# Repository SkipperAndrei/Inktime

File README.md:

# InkTime Watch

Made by: Giurgiu Andrei-Ștefan 335CA

## Cuprins

1. [Prezentare generală](#1-prezentare-generală)
2. [Diagramă bloc](#2-diagramă-bloc)
3. [BOM – Bill of Materials](#3-bom--bill-of-materials)
4. [Descrierea hardware în detaliu](#4-descrierea-hardware-în-detaliu)
5. [Pinout nRF52840 – atribuire completă](#5-pinout-nrf52840--atribuire-completă)
6. [Estimare consum de energie](#6-estimare-consum-de-energie)
7. [Arhitectura firmware](#7-arhitectura-firmware)
8. [Aplicația mobilă companion](#8-aplicația-mobilă-companion)
9. [Randări produs](#9-randări-produs)

---

## 1. Prezentare generală

**InkTime** este un smartwatch conceput pentru a oferi:

- Afișaj e-paper 1.54" (200×200 px) cu refresh parțial o dată pe minut pentru un cadran digital clar, lizibil la orice lumină.
- Notificări BLE de pe telefon (profil tipic: ≤ 50 notificări/zi) cu alerte haptic.
- Numărare pași permanentă prin accelerometru cu pedometru integrat și trezire prin întrerupere.
- Încărcare USB-C și cale robustă de recuperare/programare prin Tag-Connect TC2030 SWD.

**Principii de proiectare:**

| Principiu | Descriere |
|---|---|
| Power first | Consum mediu minimizat; design interrupt-driven; fără conexiune BLE permanentă |
| Glanceable | UI simplu, contrast ridicat, fără ecrane dense cu text |
| Deterministic | Stări de putere predictibile; cale de recuperare robustă; fără stări hardware nedefinite |
| Buildable | Asamblare SMT repetabilă (JLC) și pași de asamblare manuală expliciți |

---

## 2. Diagramă bloc

**Legendă interfețe:**

| Interfață | Componente conectate |
|---|---|
| I²C (shared bus) | BQ25180, RT6160, MAX17048, BMA421, DRV2605L |
| SPI | E-paper display controller |
| GPIO | Butoane, PFET e-paper, întreruperi (INT1/INT2 accel, ALRT fuel gauge, /INT charger) |
| USB | nRF52840 native USB (D+/D-) + VBUS detect |
| SWD | Tag-Connect TC2030 (SWDIO, SWDCLK, nRESET) |

---

## 3. BOM – Bill of Materials

| # | Funcție | Componentă | Pachet | LCSC Part | Link JLCPCB | Datasheet |
|---|---|---|---|---|---|---|
| 1 | MCU (BLE + USB) | nRF52840-QIAA-R | aQFN73 7×7 | C190794 | [JLCPCB](https://jlcpcb.com/partdetail/NordicSemiconductor-nRF52840QIAAR/C190794) | [Datasheet](https://infocenter.nordicsemi.com/pdf/nRF52840_PS_v1.7.pdf) |
| 2 | Charger / power-path | BQ25180YBGR | DSBGA-8 | C3682423 | [JLCPCB](https://jlcpcb.com/partdetail/TexasInstruments-BQ25180YBGR/C3682423) | [Datasheet](https://www.ti.com/lit/ds/symlink/bq25180.pdf) |
| 3 | Regulator 3.3V buck-boost | RT6160AWSC | WLCSP-15 | C7065276 | [JLCPCB](https://jlcpcb.com/partdetail/RichtekTech-RT6160AWSC/C7065276) | [Datasheet](https://www.richtek.com/assets/product_file/RT6160A/DS6160A-01.pdf) |
| 4 | Fuel gauge | MAX17048G+T10 | DFN-8 2×2 | C2682616 | [JLCPCB](https://jlcpcb.com/partdetail/MaximIntegrated-MAX17048GT10/C2682616) | [Datasheet](https://www.analog.com/media/en/technical-documentation/data-sheets/MAX17048-MAX17049.pdf) |
| 5 | Accelerometru / pedometru | BMA421 | LGA-12 2×2 | C5242966 | [JLCPCB](https://jlcpcb.com/partdetail/BoschSensortec-BMA421/C5242966) | [Datasheet](https://www.bosch-sensortec.com/media/boschsensortec/downloads/datasheets/bst-bma421-ds000.pdf) |
| 6 | Driver haptic | DRV2605LDGSR | VSSOP-10 | C527464 | [JLCPCB](https://jlcpcb.com/partdetail/TexasInstruments-DRV2605LDGSR/C527464) | [Datasheet](https://www.ti.com/lit/ds/symlink/drv2605l.pdf) |
| 7 | Motor vibrant ERM | LCM1027B3605F | Wire leads | C7528806 | [JLCPCB](https://jlcpcb.com/partdetail/C7528806) | [Datasheet](https://datasheet.lcsc.com/lcsc/2208251630_NOVASEN-LCM1027B3605F_C7528806.pdf) |
| 8 | PFET (power gate EPD) | SI2301CDS | SOT-23 | C10487 | [JLCPCB](https://jlcpcb.com/partdetail/Vishay-SI2301CDS/C10487) | [Datasheet](https://www.vishay.com/docs/63524/si2301cds.pdf) |
| 9 | Conector debug | Tag-Connect TC2030-IDC | PCB footprint | — | [Tag-Connect](https://www.tag-connect.com/product/tc2030-idc-nl) | [Pinout](https://www.tag-connect.com/wp-content/uploads/bsk-pdf-manager/2019/10/TC2030-IDC-NL.pdf) |
| 10 | Afișaj e-paper | 1.54" EPD 200×200 (Good Display GDEW0154M09 sau echivalent) | FPC | — | [Good Display](https://www.good-display.com) | [Datasheet](https://www.good-display.com/companyfile/459.html) |

---

## 4. Descrierea hardware în detaliu

### 4.1 MCU – nRF52840-QIAA

nRF52840 este microcontrolerul central al proiectului. Integrează:

- Procesor ARM Cortex-M4F @ 64 MHz
- Radio BLE 5.0 + IEEE 802.15.4
- USB 2.0 Full Speed nativ (D+/D-)
- 1 MB Flash, 256 KB RAM
- Periferice hardware: multiple SPI, I²C, UART, PWM, ADC, comparatoare

**Alimentare MCU:**

| Rail | Conexiune | Valoare / Notă |
|---|---|---|
| VDD (toți pinii) | VDD 3V3 | 3.3V de la RT6160 |
| VDDH | VDD 3V3 | Mod normal-voltage (nu high-voltage) |
| VSS + pad expus | GND plane | |
| DEC1 | 100nF la GND | |
| DEC4 + DEC6 | 1µF la GND | Nodul DC/DC intern REG1 |
| DECUSB | 4.7µF la GND | Filtrare USB |

**DC/DC intern (REG1):** Firmware-ul activează DCDC1 la runtime. Circuitul extern: DCC → 10µH → 15nH → nod DEC4/DEC6.

**Cristale:**

| Cristal | Pini | Scopul |
|---|---|---|
| 32 MHz | XC1 / XC2 | Sistem principal, radio BLE, USB |
| 32.768 kHz | XL1 / XL2 | RTC, timekeeping, minute tick |

Condensatorii de sarcină ai cristalelor se dimensionează în funcție de CL-ul cristalului ales (ajustare posibilă pe board).

---

### 4.2 Charger – BQ25180YBGR

BQ25180 este un charger linear/power-path pentru LiPo de până la 1A, cu interfață I²C.

**Rol în sistem:**

- Primește 5V de pe USB-C pe pinul IN.
- Oferă VSYS pe pinul SYS — rail intermediar care alimentează regulatorul RT6160.
- Gestionează încărcarea bateriei LiPo pe pinul BAT cu protecție integrată (supraîncărcare, supraîncălzire, scurtcircuit).

**Conexiuni cheie:**

| Pin BQ25180 | Conexiune |
|---|---|
| IN | VBUS 5V (USB) |
| BAT | VBAT (LiPo +) |
| SYS | VSYS → RT6160 VIN |
| SCL / SDA | I²C shared bus |
| /INT | GPIO MCU (întrerupere opțională pentru evenimente charger) |
| TS / MR | Strapped cu 10kΩ la GND (Rev A) |

**Decuplare:** CIN = 1µF, CSYS = 10µF, CBAT = 1µF (minim, dimensionate cu derating termic).

**Adresă I²C:** `0x6A`

---

### 4.3 Regulator 3.3V – RT6160AWSC

RT6160 este un convertor buck-boost care menține 3.3V fix pe toată plaja de descărcare a LiPo (de la ~4.2V până la ~3.0V și sub). Asigură că VBAT scăzut nu provoacă brownout pe MCU sau periferice.

**Conexiuni cheie:**

| Pin RT6160 | Conexiune |
|---|---|
| VIN | VSYS (ieșirea SYS a BQ25180) |
| VOUT | VDD 3V3 |
| VSEL | GND (selectează fix 3.3V) |
| EN | VSYS (always-on când VSYS e prezent) |
| SCL / SDA | I²C shared bus (opțional, pentru telemetrie / DVFS viitor) |

**Componentă externă putere:** Inductor 0.47µH, input multi-22µF, output 10µF (valori recomandate Richtek).

**Adresă I²C:** `0x75`

---

### 4.4 Fuel Gauge – MAX17048G+T10

MAX17048 măsoară tensiunea bateriei LiPo prin algoritmul ModelGauge și raportează SOC (State of Charge) în procente prin I²C.

**Conexiuni cheie:**

| Pin MAX17048 | Conexiune |
|---|---|
| BAT / VDD | VBAT |
| SDA / SCL | I²C shared bus |
| ALRT | GPIO MCU (active low, pull-up la VDD 3V3) → sursă de trezire din sleep |

**Decuplare:** 0.1µF lângă VDD.

**Adresă I²C:** `0x36`

**Funcționalitate:** Pinul ALRT generează o întrerupere când SOC scade sub pragul configurat (ex. 5%) — MCU se trezește, afișează avertisment baterie slabă și/sau inițiază BLE disconnect.

---

### 4.5 Accelerometru / Pedometru – BMA421

BMA421 este un accelerometru triaxial de înaltă performanță cu pedometru hardware integrat, optimizat pentru purtabila (consum < 200µA în mod step counter).

**Mod de operare principal:** I²C (CSB strapped high, SDO strapped low → adresă 0x18).

**Conexiuni cheie:**

| Pin BMA421 | Conexiune |
|---|---|
| VDD / VDDIO | VDD 3V3 (decuplare 0.1µF per pin) |
| SDA / SCL | I²C shared bus |
| CSB | High → mod I²C |
| SDO | Low → adresă 0x18 |
| INT1 | P0.08 → trezire primară din Deep Sleep (pas detectat, motion) |
| INT2 | P1.08 → evenimente secundare / debug |

**Funcționalitate:** Pedometrul hardware numără pași fără implicarea MCU-ului. MCU se trezește doar la întreruperea INT1 pentru a citi și cumula datele, reducând consumul la minimum.

---

### 4.6 Driver haptic – DRV2605L + Motor ERM LCM1027B3605F

DRV2605L controlează motorul vibrant ERM (Eccentric Rotating Mass) prin forme de undă preprogramate stocate în ROM intern (biblioteca Immersion HD), selectate prin I²C.

**Conexiuni cheie:**

| Pin DRV2605L | Conexiune |
|---|---|
| VDD | VDD 3V3 (decuplare locală) |
| SDA / SCL | I²C shared bus |
| EN | P0.12 → shutdown complet între evenimente haptic |
| OUT+ / OUT- | Terminalele motorului ERM |

**Adresă I²C:** `0x5A`

**Politică de consum:** EN pus LOW între evenimente haptic elimină curentul de quiescent al driverului. Motorul rulează doar pe durata unui pattern (tipic 50–300ms).

---

### 4.7 Afișaj E-paper 1.54" (200×200)

Afișajul e-paper păstrează imaginea fără consum de energie în stare statică — ideal pentru un cadran de ceas. Consumă curent doar în timpul refresh-ului.

**Interfață:** SPI + 3 GPIO de control.

**Conexiuni cheie:**

| Semnal | Pin MCU | Rol |
|---|---|---|
| SCK | P0.02 | Clock SPI |
| MOSI | P0.03 | Date SPI (write-only) |
| CS | P0.05 | Chip select |
| DC | P0.15 | Data / Command select |
| RST | P0.16 | Reset panel |
| BUSY | P0.17 | Semnal panel ocupat (polling) |
| PFET gate | P1.01 | Power gate VEPD (prin rezistor 100Ω; pull-up 100kΩ gate-source) |

**Power gating VEPD:** Un P-FET (SI2301CDS) comutează alimentarea afișajului (VEPD) din VDD 3V3. Firmware-ul poate dezactiva VEPD complet între refresh-uri pentru a elimina curentul de leakage al display-ului și al FPC.

**Politică refresh:**

- Refresh parțial la fiecare minut (time update) — consum minim, fără ghosting vizibil pe termen scurt.
- Refresh complet la intervale configurabile (ex. la fiecare oră sau la cerere) pentru eliminarea ghosting-ului acumulat.

**Rezistori de serie opționali (DNP):** 100Ω–1kΩ pe liniile SPI/control pentru a reduce riscul de back-power când VEPD este dezactivat.

---

### 4.8 Butoane

Trei butoane mecanice active-low:

| Buton | Pin MCU | Conexiune |
|---|---|---|
| UP | P0.13 | GPIO → Switch → GND |
| DOWN | P0.14 | GPIO → Switch → GND |
| ENTER / ESC | P1.00 | GPIO → Switch → GND |

Firmware-ul activează pull-up intern pe fiecare pin și configurează wake-on-low + debounce software (tipic 20–50ms).

---

### 4.9 Interfața de programare – Tag-Connect TC2030 SWD

| Pin TC2030 | Semnal |
|---|---|
| 1 | VTref (VDD 3V3) — referință tensiune pentru debugger |
| 2 | SWDIO |
| 3 | GND |
| 4 | SWDCLK |
| 5 | GND |
| 6 | nRESET |

Board-ul este self-powered (baterie sau USB); TC2030 nu trebuie să furnizeze curent. VTref este obligatoriu pentru ca debugger-ul să detecteze tensiunea I/O a target-ului.

---

## 5. Pinout nRF52840 – atribuire completă

| Pin nRF52840 | Funcție | Componentă / Semnal | Justificare alegere |
|---|---|---|---|
| P0.02 | SPI SCK | E-paper clock | SPI0 hardware; alocare convenabilă pentru routing PCB |
| P0.03 | SPI MOSI | E-paper date | SPI0 hardware |
| P0.05 | SPI CS | E-paper chip select | GPIO flexibil, contiguitate cu celelalte pini SPI |
| P0.06 | I²C SDA | Bus I²C shared | I2C0 hardware Nordic; pull-up extern 10kΩ |
| P0.07 | I²C SCL | Bus I²C shared | I2C0 hardware Nordic; pull-up extern 10kΩ |
| P0.08 | GPIO INPUT | BMA421 INT1 | Capacitate sense GPIO → wake din Deep Sleep; pin cu DETECT |
| P0.12 | GPIO OUTPUT | DRV2605L EN | Control shutdown haptic; GPIO simplu sufficient |
| P0.13 | GPIO INPUT | Buton UP | Sense GPIO, wake-on-low, pull-up intern |
| P0.14 | GPIO INPUT | Buton DOWN | Sense GPIO, wake-on-low, pull-up intern |
| P0.15 | GPIO OUTPUT | EPD DC | Control Data/Command display; GPIO rapid |
| P0.16 | GPIO OUTPUT | EPD RST | Reset panel; GPIO simplu |
| P0.17 | GPIO INPUT | EPD BUSY | Polling stare panel; GPIO simplu |
| P1.00 | GPIO INPUT | Buton ENTER/ESC | Sense GPIO, wake-on-low, pull-up intern |
| P1.01 | GPIO OUTPUT | PFET gate VEPD | Control alimentare afișaj; pull-up extern gate-source (default OFF) |
| P1.08 | GPIO INPUT | BMA421 INT2 | Eveniment secundar accelerometru / debug |
| USBDP / USBDM | USB D+ / D- | USB-C conector | Pereche diferențială native USB nRF52840; ESD lângă conector |
| VBUS | USB VBUS detect | USB 5V | Detecție attach/detach USB |
| SWDIO / SWDCLK | SWD | TC2030 pin 2 / 4 | Programare și debug hardware |
| nRESET | Reset | TC2030 pin 6 | Resetare externă prin debugger |
| XC1 / XC2 | Crystal 32 MHz | Cristal extern | Ceas sistem, radio BLE, USB |
| XL1 / XL2 | Crystal 32.768 kHz | Cristal RTC extern | RTC, minute tick, sleep scheduling |
| DEC1 | Decuplare | 100nF → GND | Rail intern nRF |
| DEC4 / DEC6 | Decuplare DC/DC | 1µF → GND | Nod inductor DC/DC REG1 |
| DECUSB | Decuplare USB | 4.7µF → GND | Filtrare rail USB intern |

**Bus I²C – hartă adrese (7-bit):**

| Adresă | Dispozitiv |
|---|---|
| 0x18 | BMA421 (accelerometru) |
| 0x36 | MAX17048 (fuel gauge) |
| 0x5A | DRV2605L (haptic driver) |
| 0x6A | BQ25180 (charger) |
| 0x75 | RT6160 (regulator) |

---

## 6. Estimare consum de energie

### 6.1 Profilul tipic de utilizare

| Eveniment | Frecvență | Energie estimată |
|---|---|---|
| Refresh parțial e-paper | 1×/minut | ~5–15 mJ/refresh |
| Notificare BLE + haptic + display | 50×/zi | ~10–20 mJ/eveniment |
| Step counter (BMA421) | continuu (MCU dormit) | ~5–10 µA curent static BMA421 |
| Deep Sleep MCU | majoritar | ~3–5 µA (MCU) + RTC |

### 6.2 Buget curent mediu (estimat)

| Componentă | Curent mediu estimat |
|---|---|
| nRF52840 Deep Sleep + RTC | ~3 µA |
| BMA421 step counter mode | ~5 µA |
| MAX17048 activ | ~23 µA |
| E-paper (static, VEPD off) | ~0 µA |
| E-paper refresh (parțial, 1/min, pulsed) | ~150–300 µA mediat pe minut |
| **Total estimat mediu** | **~180–340 µA** |

---

## 7. Arhitectura firmware

### 7.1 Stack

- **RTOS:** Zephyr OS (recomandat pentru maturitate BLE stack) sau event loop lightweight.
- **Limbaj:** C / C++ (Zephyr NCS).

### 7.2 Module principale

| Modul | Responsabilități |
|---|---|
| HAL | GPIO, I²C, SPI, timere, întreruperi, watchdog |
| Power Manager | Stări sleep, surse wake, duty cycles, power gating display |
| Timekeeping | RTC, timezone, sincronizare timp, planificare minute tick |
| Display Driver | Init, refresh parțial/complet, frame buffer, polling BUSY |
| BLE Manager | Advertising, conexiune, servicii GATT, notificări, bonding |
| Notification Service | Coadă mesaje, deduplicare, politică render, trigger haptic |
| Activity Service | Init BMA421, citire pași, reset zilnic |
| Battery Service | Citiri MAX17048, alerte baterie slabă, stare charger BQ25180 |
| Haptics Service | Init DRV2605L, pattern-uri, politică enable/disable |
| Storage | NVM pentru setări, istoric pași, preferințe notificări |
| Diagnostics | Log-uri debug, info build, hook-uri self-test |

### 7.3 Stări de putere și surse de trezire

```
┌─────────────┐   RTC tick / Button / INT / BLE event  ┌──────────────┐
│  Deep Sleep  │──────────────────────────────────────►│   Active      │
│ (radio off)  │◄──────────────────────────────────────│ (render/BLE)  │
└─────────────┘           Task complet                 └──────────────┘
        ▲                                                      │
        │                   Idle/Standby                       │
        └──────────────────────────────────────────────────────┘
```

**Surse de trezire din Deep Sleep:**

- RTC minute tick
- Butoane (GPIO sense)
- BMA421 INT1/INT2 (pași/mișcare)
- MAX17048 ALRT (prag baterie slabă)
- BQ25180 /INT (eveniment charger)
- BLE events (ferestre programate)

### 7.4 Servicii BLE GATT (MVP)

| Serviciu | UUID | Descriere |
|---|---|---|
| Device Information (DIS) | Standard | Model, versiune firmware |
| Battery Service (BAS) | Standard | Procent baterie (MAX17048) |
| Custom Notification Service | Custom | Push notificări, clear, ack |
| Time Sync | Custom | Setare oră/timezone; proxy NTP opțional |
| DFU Service | Custom (opțional) | Update firmware OTA |

**Payload notificare:** timestamp, app id, titlu, corp (trunchiat), prioritate, vibration pattern id — optimizat pentru BLE MTU cu suport chunking.

---

## 8. Aplicația mobilă companion

### 8.1 Strategie platformă

- MVP: o platformă prima (Android sau iOS), cu plan clar de paritate.
- Cross-platform: Flutter sau React Native dacă cerințele BLE stack sunt satisfăcute.
- Native: Kotlin (Android) / Swift (iOS) pentru fiabilitate BLE maximă.

### 8.2 Module app

| Modul | Responsabilități |
|---|---|
| BLE Transport | Scan, connect, bonding, MTU, reconectare, comportament background |
| Device Model | Stare cached: baterie, firmware, setări, last seen |
| Notification Bridge | Capturare notificări OS, filtrare, formatare, coadă send |
| Settings UI | Allowlist/blocklist, ore liniștite, pattern-uri vibrație |
| Time Service | Sincronizare oră + timezone, politică drift |
| DFU/Update | Download/verify firmware, transfer, progres, rollback |

### 8.3 Pipeline notificări

```
Eveniment OS → Filtrare reguli (app list, quiet hours) → Render payload compact →
→ Coadă cu retry/backoff (dacă watch deconectat) → Send BLE → Ack opțional
```

---

### 9 Randări produs

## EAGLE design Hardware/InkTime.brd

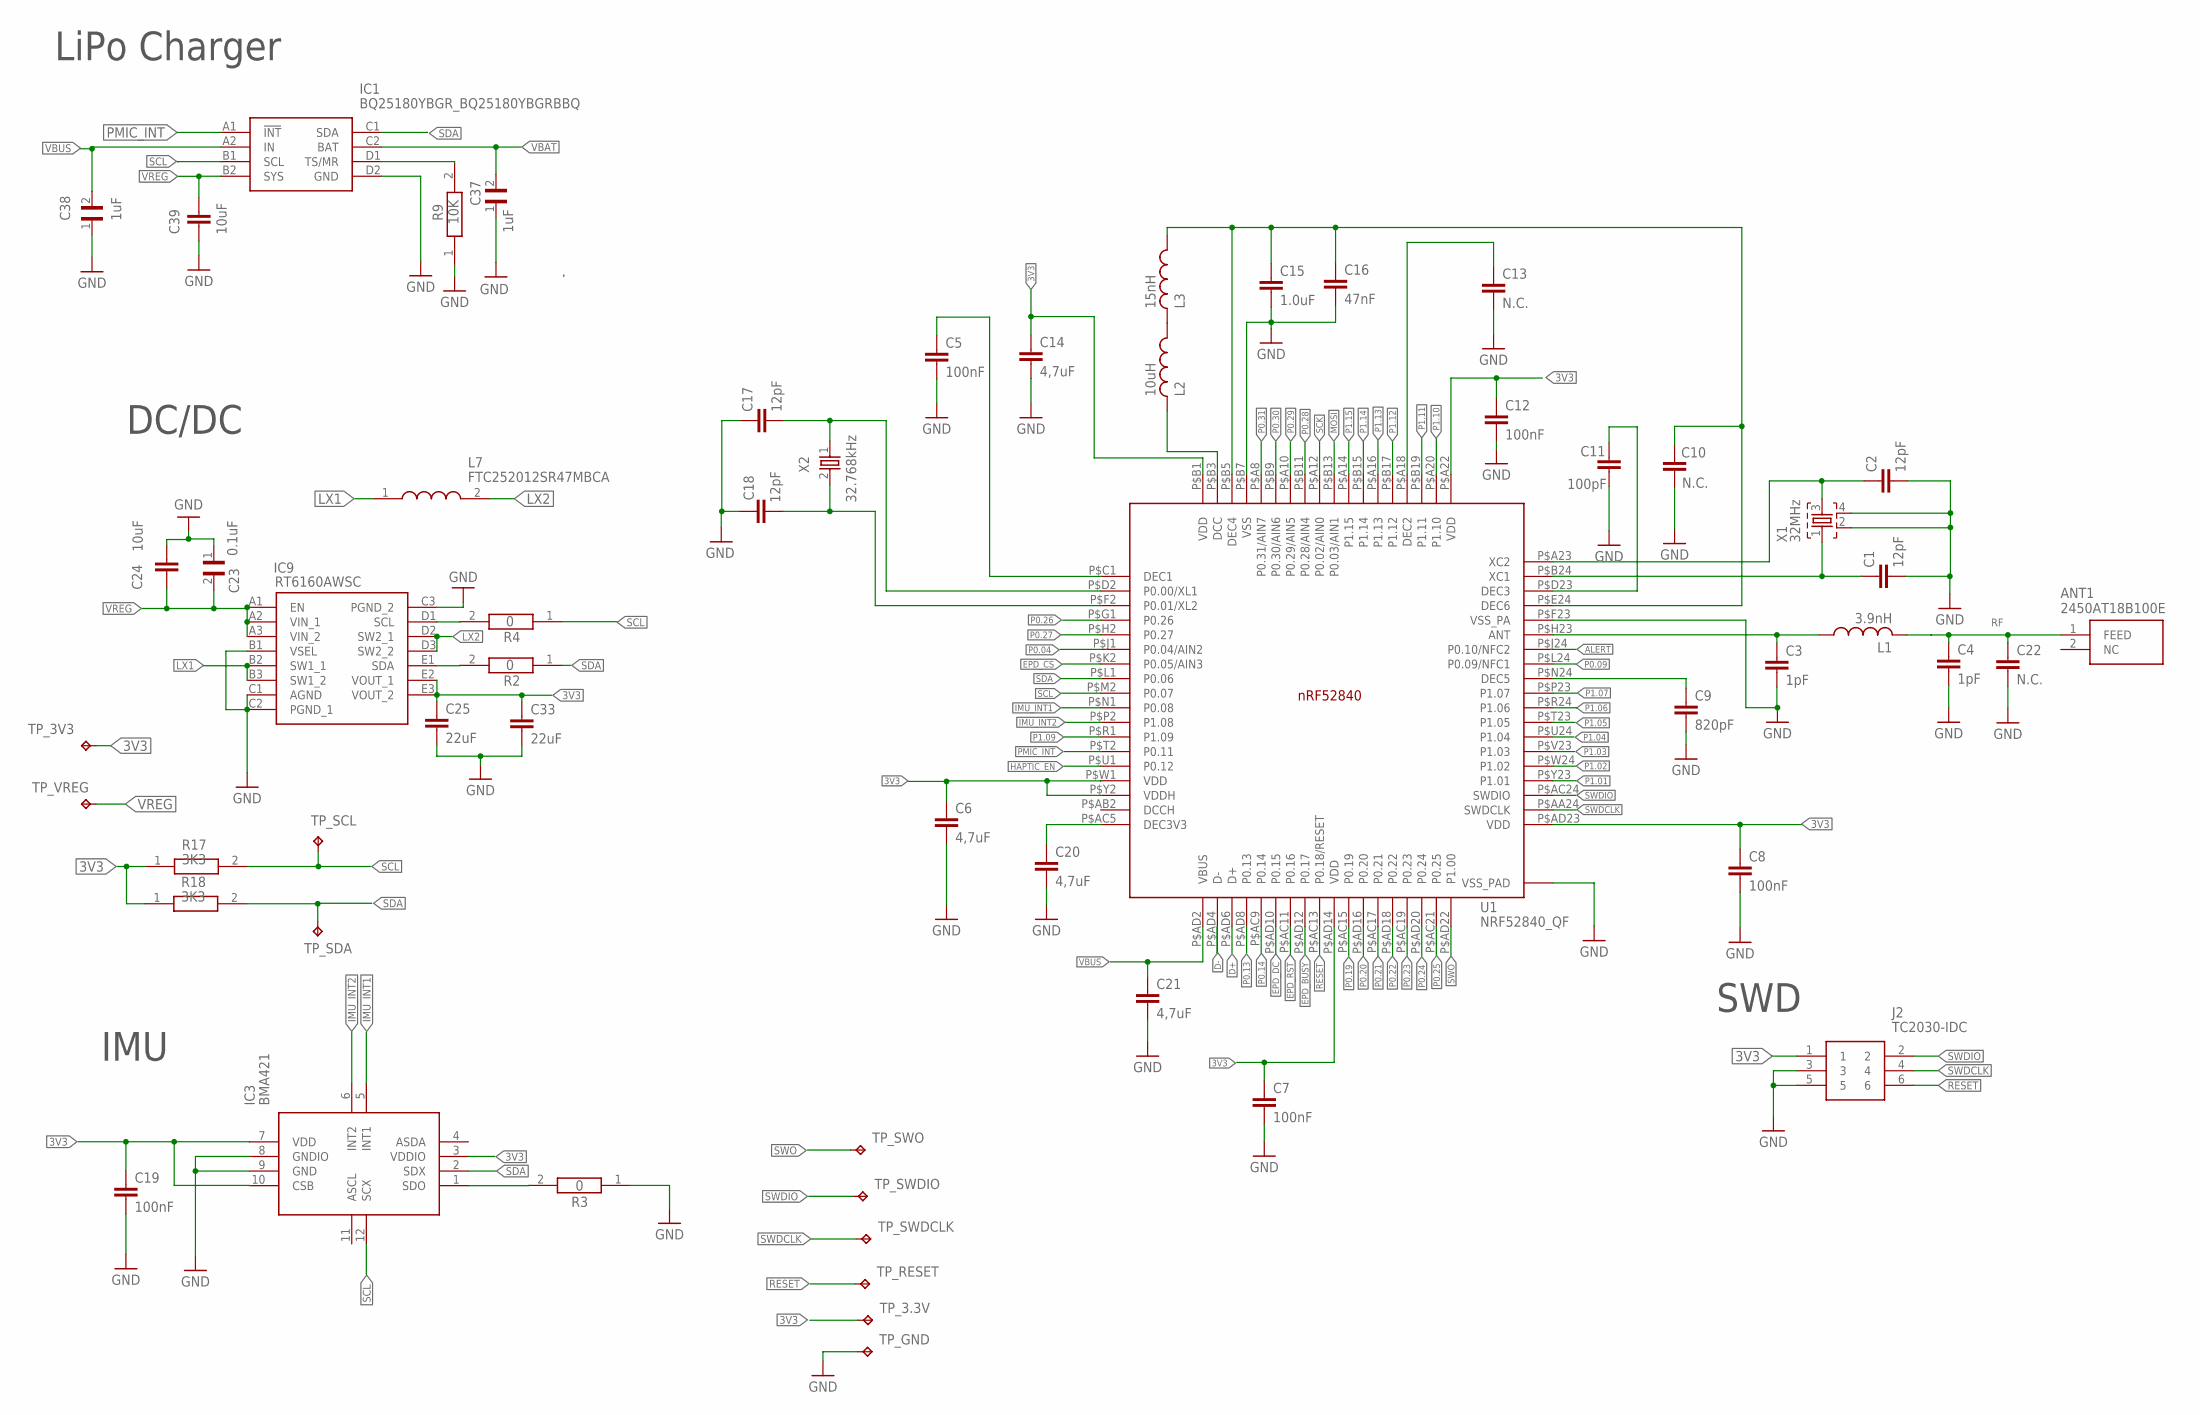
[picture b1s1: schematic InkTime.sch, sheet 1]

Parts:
ANT1: 2450AT18B100E; 2450AT18B100E_ANTC3216X140N
C1, C2, C17, C18: 12pF; NORDIC_NRF_3_RESC0201_N
C3, C4: 1pF; NORDIC_NRF_3_RESC0201_N
C5, C7, C8, C12, C19: 100nF; NORDIC_NRF_3_RESC0201_N
C6, C14, C20, C21: 4,7uF; NORDIC_NRF_3_RESC0402_N
C9: 820pF; NORDIC_NRF_3_RESC0201_N
C10, C13, C22: N.C.; NORDIC_NRF_3_RESC0201_N
C11: 100pF; NORDIC_NRF_3_RESC0201_N
C15: 1.0uF; NORDIC_NRF_3_RESC0402_N
C16: 47nF; NORDIC_NRF_3_RESC0201_N
C23: 0.1uF; GRM011R60J152KE01L_2_CAPC0201X13N
C24, C39: 10uF; NORDIC_NRF_3_RESC0402_N
C25, C33: 22uF; NORDIC_NRF_3_RESC0402_N
C37, C38: 1uF; GRM011R60J152KE01L_2_CAPC0201X13N
IC1: BQ25180YBGR_BQ25180YBGRBBQ; BQ25180YBGR_BGA8C40P2X4_100X155X50
IC3: BMA421; BMA423_BMA423
IC9: RT6160AWSC; RT6160AWSC_BGA15C40P3X5_140X230X60
J2: TC2030-IDC; TC2030-IDC_TC2030IDC
L1: 3.9nH; NORDIC_NRF_2_RESC0201_N
L2: 10uH; NORDIC_NRF_2_RESC0201_N
L3: 15nH; NORDIC_NRF_2_RESC0201_N
L7: FTC252012SR47MBCA; MLP2016SR47MT0S1_INDC2016X100N
R2, R3, R4: 0; CPF0201D7K68C1_0201
R9: 10K; CPF0201D7K68C1_0201
R17, R18: 3K3; CPF0201D7K68C1_0201
TP_3.3V, TP_3V3: HECTOR_WATCH_1_TPTP20R; HECTOR_WATCH_1_TP20R
TP_GND: HECTOR_WATCH_1_TPTP20R; HECTOR_WATCH_1_TP20R
TP_RESET: HECTOR_WATCH_1_TPTP20R; HECTOR_WATCH_1_TP20R
TP_SCL: HECTOR_WATCH_1_TPTP20R; HECTOR_WATCH_1_TP20R
TP_SDA: HECTOR_WATCH_1_TPTP20R; HECTOR_WATCH_1_TP20R
TP_SWDCLK: HECTOR_WATCH_1_TPTP20R; HECTOR_WATCH_1_TP20R
TP_SWDIO: HECTOR_WATCH_1_TPTP20R; HECTOR_WATCH_1_TP20R
TP_SWO: HECTOR_WATCH_1_TPTP20R; HECTOR_WATCH_1_TP20R
TP_VREG: HECTOR_WATCH_1_TPTP20R; HECTOR_WATCH_1_TP20R
U1: NRF52840_QF; NORDIC_NRF_4_AQFN50P700X700X85_HS-74N
X1: 32MHz; NORDIC_NRF_BT-XTAL_2016_N
X2: 32.768kHz; NORDIC_NRF_1_XTAL_3215_N

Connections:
3V3: C6.1, C7.1, C8.1, C12.1, C14.1, C19.1, C25.1, C33.1, IC3.3 (VDDIO), IC3.7 (VDD), IC3.10 (CSB), IC9.E2 (VOUT_1), IC9.E3 (VOUT_2), J2.1, R17.1, R18.1, TP_3.3V.TP, TP_3V3.TP, U1.P$A22 (VDD), U1.P$AD14 (VDD), U1.P$AD23 (VDD), U1.P$B1 (VDD), U1.P$W1 (VDD), U1.P$Y2 (VDDH); also elsewhere on the board
ALERT: U1.P$J24 (P0.10/NFC2); also elsewhere on the board
D+: U1.P$AD6 (D+); also elsewhere on the board
D-: U1.P$AD4 (D-); also elsewhere on the board
EPD_BUSY: U1.P$AD12 (P0.17); also elsewhere on the board
EPD_CS: U1.P$K2 (P0.05/AIN3); also elsewhere on the board
EPD_DC: U1.P$AD10 (P0.15); also elsewhere on the board
EPD_RST: U1.P$AC11 (P0.16); also elsewhere on the board
GND: C1.2, C2.2, C3.2, C4.2, C5.2, C6.2, C7.2, C8.2, C9.2, C10.2, C11.2, C12.2, C13.2, C14.2, C15.2, C16.2, C17.1, C18.2, C19.2, C20.2, C21.2, C22.2, C23.1, C24.1, C25.2, C33.2, C37.1, C38.1, C39.2, IC1.D2 (GND), IC3.8 (GNDIO), IC3.9 (GND), IC9.B1 (VSEL), IC9.C1 (AGND), IC9.C2 (PGND_1), IC9.C3 (PGND_2), J2.3, J2.5, R3.1, R9.1, TP_GND.TP, U1.P$74 (VSS_PAD), U1.P$75 (VSS_PAD), U1.P$76 (VSS_PAD), U1.P$77 (VSS_PAD), U1.P$78 (VSS_PAD), U1.P$79 (VSS_PAD), U1.P$80 (VSS_PAD), U1.P$81 (VSS_PAD), U1.P$82 (VSS_PAD), U1.P$83 (VSS_PAD), U1.P$84 (VSS_PAD), U1.P$85 (VSS_PAD), U1.P$86 (VSS_PAD), U1.P$87 (VSS_PAD), U1.P$88 (VSS_PAD), U1.P$89 (VSS_PAD), U1.P$90 (VSS_PAD), U1.P$B7 (VSS), U1.P$F23 (VSS_PA), X1.2, X1.4; also elsewhere on the board
HAPTIC_EN: U1.P$U1 (P0.12); also elsewhere on the board
IMU_INT1: IC3.5 (INT1), U1.P$N1 (P0.08)
IMU_INT2: IC3.6 (INT2), U1.P$P2 (P1.08)
LX1: IC9.B2 (SW1_1), IC9.B3 (SW1_2), L7.1
LX2: IC9.D2 (SW2_1), IC9.D3 (SW2_2), L7.2
MOSI: U1.P$B13 (P0.03/AIN1); also elsewhere on the board
unnamed: IC1.D1 (TS/MR), R9.2
unnamed: IC9.D1 (SCL), R4.2
unnamed: IC9.E1 (SDA), R2.2
unnamed: IC3.1 (SDO), R3.2
unnamed: C9.1, U1.P$N24 (DEC5)
unnamed: C3.1, L1.1, U1.P$H23 (ANT)
unnamed: C11.1, U1.P$D23 (DEC3)
unnamed: C10.1, C15.1, C16.1, L3.1, U1.P$B5 (DEC4), U1.P$E24 (DEC6)
unnamed: C2.1, U1.P$A23 (XC2), X1.3
unnamed: C1.1, U1.P$B24 (XC1), X1.1
unnamed: C13.1, U1.P$A18 (DEC2)
unnamed: L2.1, L3.2
unnamed: L2.2, U1.P$B3 (DCC)
unnamed: C5.1, U1.P$C1 (DEC1)
unnamed: C17.2, U1.P$D2 (P0.00/XL1), X2.1
unnamed: C18.1, U1.P$F2 (P0.01/XL2), X2.2
unnamed: C20.1, U1.P$AC5 (DEC3V3)
P0.04: U1.P$J1 (P0.04/AIN2)
P0.09: U1.P$L24 (P0.09/NFC1)
P0.13: U1.P$AD8 (P0.13); also elsewhere on the board
P0.14: U1.P$AC9 (P0.14); also elsewhere on the board
P0.19: U1.P$AC15 (P0.19)
P0.20: U1.P$AD16 (P0.20)
P0.21: U1.P$AC17 (P0.21)
P0.22: U1.P$AD18 (P0.22)
P0.23: U1.P$AC19 (P0.23)
P0.24: U1.P$AD20 (P0.24)
P0.25: U1.P$AC21 (P0.25)
P0.26: U1.P$G1 (P0.26)
P0.27: U1.P$H2 (P0.27)
P0.28: U1.P$B11 (P0.28/AIN4)
P0.29: U1.P$A10 (P0.29/AIN5)
P0.30: U1.P$B9 (P0.30/AIN6)
P0.31: U1.P$A8 (P0.31/AIN7)
P1.01: U1.P$Y23 (P1.01); also elsewhere on the board
P1.02: U1.P$W24 (P1.02); also elsewhere on the board
P1.03: U1.P$V23 (P1.03)
P1.04: U1.P$U24 (P1.04)
P1.05: U1.P$T23 (P1.05)
P1.06: U1.P$R24 (P1.06)
P1.07: U1.P$P23 (P1.07)
P1.09: U1.P$R1 (P1.09)
P1.10: U1.P$A20 (P1.10)
P1.11: U1.P$B19 (P1.11)
P1.12: U1.P$B17 (P1.12)
P1.13: U1.P$A16 (P1.13)
P1.14: U1.P$B15 (P1.14)
P1.15: U1.P$A14 (P1.15)
PMIC_INT: IC1.A1 (!INT), U1.P$T2 (P0.11)
RESET: J2.6, TP_RESET.TP, U1.P$AC13 (P0.18/RESET)
RF: ANT1.1 (FEED), C4.1, C22.1, L1.2
SCK: U1.P$A12 (P0.02/AIN0); also elsewhere on the board
SCL: IC1.B1 (SCL), IC3.12 (SCX), R4.1, R17.2, TP_SCL.TP, U1.P$M2 (P0.07); also elsewhere on the board
SDA: IC1.C1 (SDA), IC3.2 (SDX), R2.1, R18.2, TP_SDA.TP, U1.P$L1 (P0.06); also elsewhere on the board
SWDCLK: J2.4, TP_SWDCLK.TP, U1.P$AA24 (SWDCLK)
SWDIO: J2.2, TP_SWDIO.TP, U1.P$AC24 (SWDIO)
SWO: TP_SWO.TP, U1.P$AD22 (P1.00)
VBAT: C37.2, IC1.C2 (BAT); also elsewhere on the board
VBUS: C21.1, C38.2, IC1.A2 (IN), U1.P$AD2 (VBUS); also elsewhere on the board
VREG: C23.2, C24.2, C39.1, IC1.B2 (SYS), IC9.A1 (EN), IC9.A2 (VIN_1), IC9.A3 (VIN_2), TP_VREG.TP

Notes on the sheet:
LiPo Charger
DC/DC
IMU
SWD

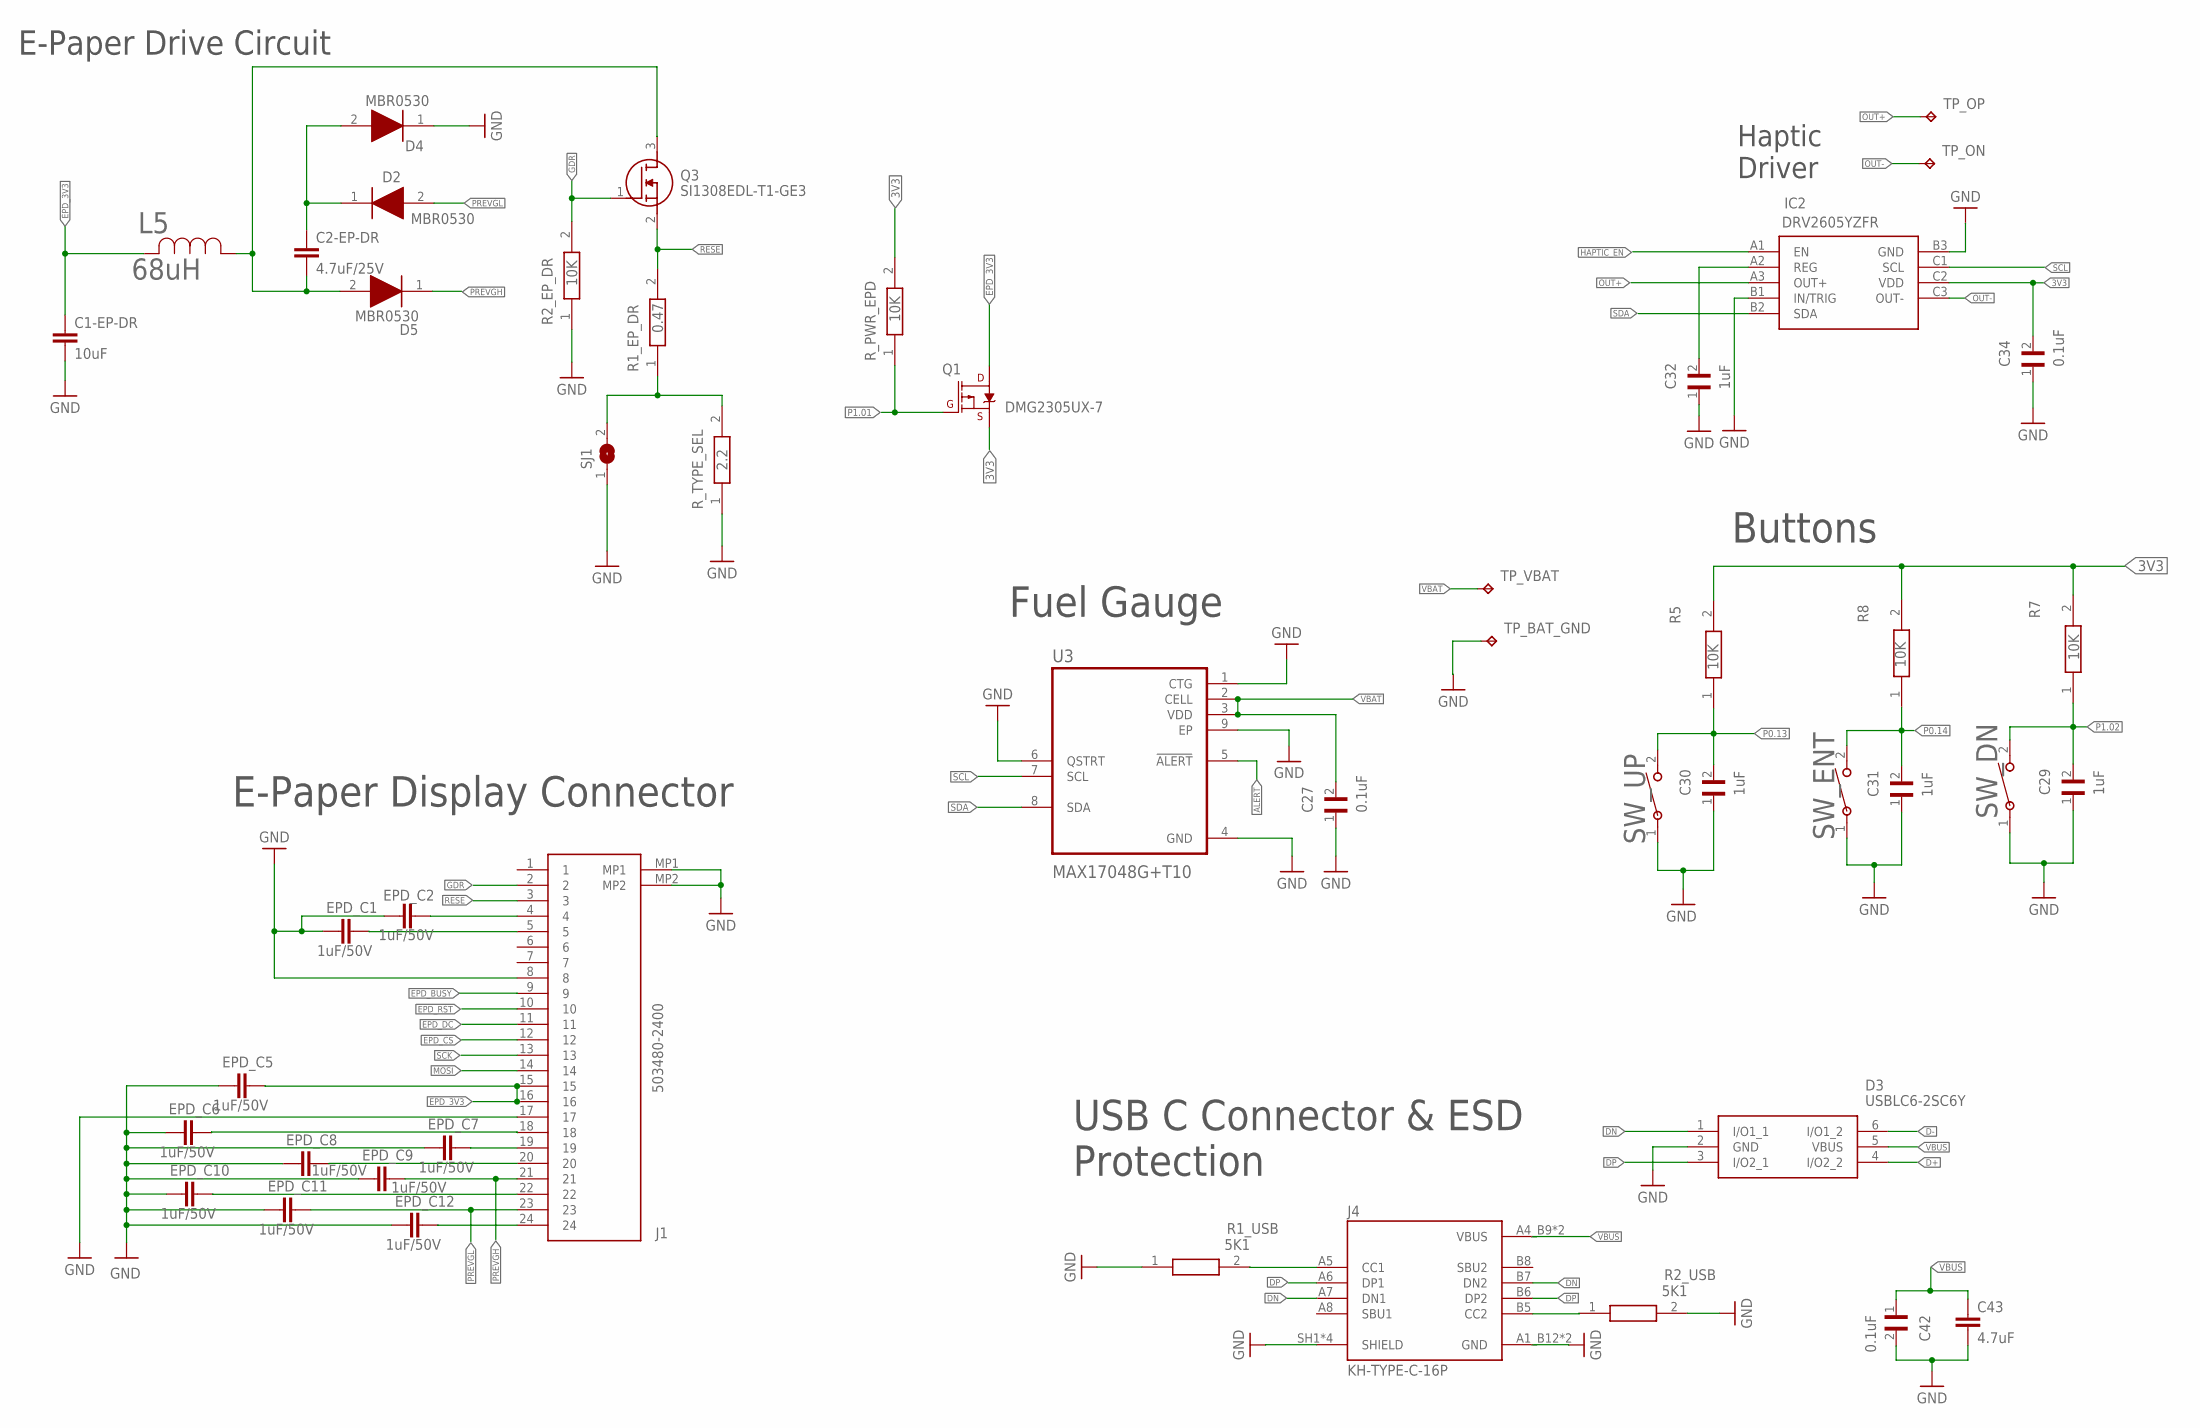
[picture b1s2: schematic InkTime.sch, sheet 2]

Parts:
C1-EP-DR: 10uF; NORDIC_NRF_3_RESC0402_N
C2-EP-DR: 4.7uF/25V; NORDIC_NRF_3_RESC0402_N
C27, C34, C42: 0.1uF; GRM011R60J152KE01L_2_CAPC0201X13N
C29, C30, C31, C32: 1uF; GRM011R60J152KE01L_2_CAPC0201X13N
C43: 4.7uF; NORDIC_NRF_3_RESC0402_N
D2, D4, D5: MBR0530; ESP32_C6_LIBRARY_5_SOD3716X135N
D3: USBLC6-2SC6Y; ESP32_C6_LIBRARY_3_SOT95P280X145-6N
EPD_C1, EPD_C2, EPD_C5, EPD_C6, EPD_C7, EPD_C8, EPD_C9, EPD_C10, EPD_C11, EPD_C12: 1uF/50V; NORDIC_NRF_3_RESC0402_N
IC2: DRV2605YZFR; DRV2605YZFR_BGA9C50P3X3_144X144X62
J1: 503480-2400; 503480-2400_5034802400
J4: KH-TYPE-C-16P; KH-TYPE-C-16P_KINGHELM_KH-TYPE-C-16P
L5: 68uH; ESP32_C6_LIBRARY_2_IND_4828-WE-TPC_WRE
Q1: DMG2305UX-7; ESP32_C6_LIBRARY_4_ESP32_C6_LIBRARY_4_ESP32_C6_LIBRARY_4_ES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
Q3: SI1308EDL-T1-GE3; ESP32_C6_LIBRARY_6_SOT65P210X110-3N
R1_EP_DR: 0.47; CPF0201D7K68C1_0201
R1_USB, R2_USB: 5K1; CPF0201D7K68C1_0201
R2_EP_DR, R5, R7, R8: 10K; CPF0201D7K68C1_0201
R_PWR_EPD: 10K; CPF0201D7K68C1_0201
R_TYPE_SEL: 2.2; CPF0201D7K68C1_0201
SJ1: ESP32_C6_LIBRARY_7_JUMPER_SJ
SW_DN: 2025-10-22_07-23-44_LIBRARY_EVP-AKE31A; 2025-10-22_07-23-44_LIBRARY_SW_EVP-AKE31A_PAN
SW_ENT: 2025-10-22_07-23-44_LIBRARY_EVP-AKE31A; 2025-10-22_07-23-44_LIBRARY_SW_EVP-AKE31A_PAN
SW_UP: 2025-10-22_07-23-44_LIBRARY_EVP-AKE31A; 2025-10-22_07-23-44_LIBRARY_SW_EVP-AKE31A_PAN
TP_BAT_GND: HECTOR_WATCH_1_TPTP20R; HECTOR_WATCH_1_TP20R
TP_ON: HECTOR_WATCH_1_TPTP20R; HECTOR_WATCH_1_TP20R
TP_OP: HECTOR_WATCH_1_TPTP20R; HECTOR_WATCH_1_TP20R
TP_VBAT: HECTOR_WATCH_1_TPTP20R; HECTOR_WATCH_1_TP20R
U3: MAX17048G+T10; ESP32_C6_LIBRARY_SON50P200X200X80-9N

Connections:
3V3: C34.2, IC2.C2 (VDD), Q1.2 (S), R5.2, R7.2, R8.2, R_PWR_EPD.2; also elsewhere on the board
ALERT: U3.5 (!ALERT); also elsewhere on the board
D+: D3.4 (I/O2_2); also elsewhere on the board
D-: D3.6 (I/O1_2); also elsewhere on the board
DN: D3.1 (I/O1_1), J4.A7 (DN1), J4.B7 (DN2)
DP: D3.3 (I/O2_1), J4.A6 (DP1), J4.B6 (DP2)
EPD_3V3: C1-EP-DR.1, EPD_C5.2, J1.15, J1.16, L5.2, Q1.3 (D)
EPD_BUSY: J1.9; also elsewhere on the board
EPD_CS: J1.12; also elsewhere on the board
EPD_DC: J1.11; also elsewhere on the board
EPD_RST: J1.10; also elsewhere on the board
GDR: J1.2, Q3.1 (G), R2_EP_DR.2
GND: C1-EP-DR.2, C27.1, C29.1, C30.1, C31.1, C32.1, C34.1, C42.2, C43.2, D3.2 (GND), D4.1 (K), EPD_C1.1, EPD_C2.1, EPD_C5.1, EPD_C6.1, EPD_C7.1, EPD_C8.1, EPD_C9.1, EPD_C10.1, EPD_C11.1, EPD_C12.1, IC2.B1 (IN/TRIG), IC2.B3 (GND), J1.8, J1.17, J1.MP1, J1.MP2, J4.A1_B12 (GND), J4.A12_B1 (GND), J4.SH1 (SHIELD), J4.SH2 (SHIELD), J4.SH3 (SHIELD), J4.SH4 (SHIELD), R1_USB.1, R2_EP_DR.1, R2_USB.2, R_TYPE_SEL.1, SJ1.1, SW_DN.1, SW_ENT.1, SW_UP.1, TP_BAT_GND.TP, U3.1 (CTG), U3.4 (GND), U3.6 (QSTRT), U3.9 (EP); also elsewhere on the board
HAPTIC_EN: IC2.A1 (EN); also elsewhere on the board
MOSI: J1.14; also elsewhere on the board
unnamed: C32.2, IC2.A2 (REG)
unnamed: J4.A5 (CC1), R1_USB.2
unnamed: J4.B5 (CC2), R2_USB.1
unnamed: C2-EP-DR.2, D5.2 (A), L5.1, Q3.3 (D)
unnamed: C2-EP-DR.1, D2.1 (K), D4.2 (A)
unnamed: R1_EP_DR.1, R_TYPE_SEL.2, SJ1.2
unnamed: EPD_C2.2, J1.4
unnamed: EPD_C1.2, J1.5
unnamed: EPD_C6.2, J1.18
unnamed: EPD_C7.2, J1.19
unnamed: EPD_C8.2, J1.20
unnamed: EPD_C10.2, J1.22
unnamed: EPD_C12.2, J1.24
OUT+: IC2.A3 (OUT+), TP_OP.TP
OUT-: IC2.C3 (OUT-), TP_ON.TP
P0.13: C30.2, R5.1, SW_UP.2; also elsewhere on the board
P0.14: C31.2, R8.1, SW_ENT.2; also elsewhere on the board
P1.01: Q1.1 (G), R_PWR_EPD.1; also elsewhere on the board
P1.02: C29.2, R7.1, SW_DN.2; also elsewhere on the board
PREVGH: D5.1 (K), EPD_C9.2, J1.21
PREVGL: D2.2 (A), EPD_C11.2, J1.23
RESE: J1.3, Q3.2 (S), R1_EP_DR.2
SCK: J1.13; also elsewhere on the board
SCL: IC2.C1 (SCL), U3.7 (SCL); also elsewhere on the board
SDA: IC2.B2 (SDA), U3.8 (SDA); also elsewhere on the board
VBAT: C27.2, TP_VBAT.TP, U3.2 (CELL), U3.3 (VDD); also elsewhere on the board
VBUS: C42.1, C43.1, D3.5 (VBUS), J4.A4_B9 (VBUS), J4.A9_B4 (VBUS); also elsewhere on the board

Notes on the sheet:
Fuel Gauge
Haptic Driver
Buttons
USB C Connector & ESD Protection
E-Paper Drive Circuit
E-Paper Display Connector

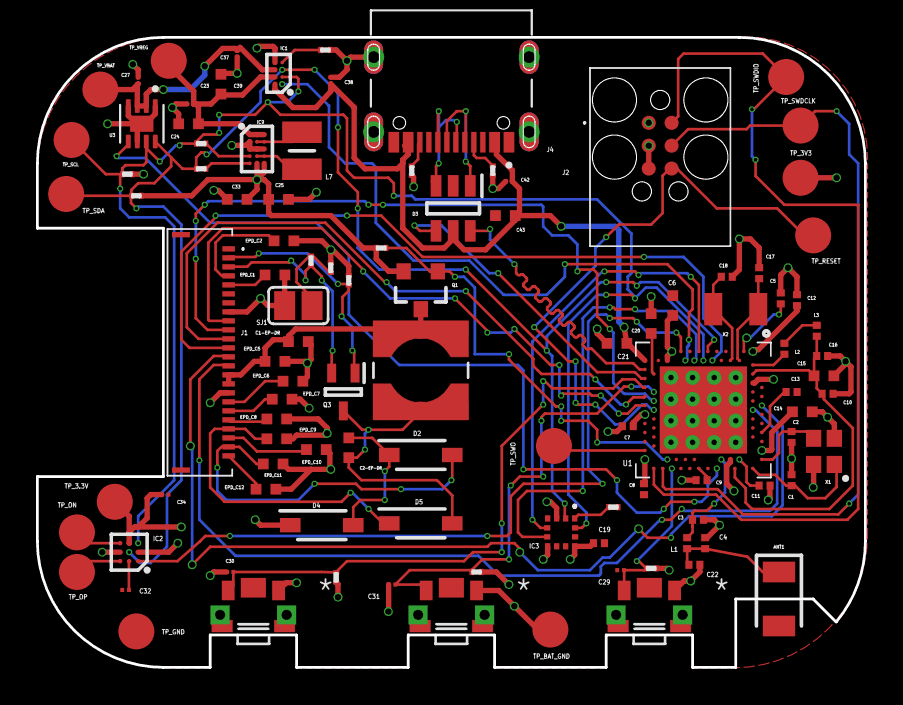
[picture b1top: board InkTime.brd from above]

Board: 4 copper layers, 46.0 x 35.0 mm, 105 parts (0 on the bottom side), 70 nets.

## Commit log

2026-04-10 Add Mechanical folder
2026-04-10 Add Manufacturing folder
2026-04-10 Add Hardware folder
2026-04-10 Add Images folder
2026-04-17 Add PCB with silkscreen layer
2026-04-20 Add README.md and block scheme
2026-04-20 Update README.md
    Removed estimated battery life information from README.
2026-04-20 Fixed minor schematic and board issues
2026-04-20 Add new Pick and Place file
2026-04-21 Add printout of schematic
2026-04-21 Fix small overlap

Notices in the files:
parts and their libraries:
COPYRIGHT: Copyright (C) 2024 Ultra Librarian. All rights reserved.
InkTime_v5: COPYRIGHT: Copyright (C) 2025 Ultra Librarian. All rights reserved.
